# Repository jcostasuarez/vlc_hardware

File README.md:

# VLC Hardware — Comunicación por Luz Visible

Hardware abierto (KiCad) de una cadena de comunicación por luz visible (VLC):
transmisor óptico, receptor óptico de alta sensibilidad y placas de
acondicionamiento RF. Proyecto final de la carrera de Ingeniería Electrónica,
UTN FRBA.

Cada placa es un módulo independiente que se interconecta con cables coaxiales
SMA de 50 Ω. Todos los proyectos son **autocontenidos**: las huellas y los
símbolos están embebidos y copiados en la biblioteca local de cada proyecto, de
modo que se abren y verifican sin depender de bibliotecas externas.

## Arquitectura

```
Transmisor:   PRE ──► AMP ─┐
                         ├──► LED ──► (espacio libre, luz IR)
              PRE ──► FCA ─┘

Receptor:     PD ──► TIA ──► rx_amp ──► osciloscopio / ADC
```

- **TX**: `PRE` (red de preénfasis) excita a `AMP` **o** a `FCA`; el driver
  elegido alimenta la placa `LED`.
- **RX**: `PD` (fotodiodo + bias) entra a **una sola** placa `TIA`
  (`LMH34400` **o** `LTC6268-10`) y su salida pasa por `rx_amp`.
- **No instalar ambas TIA** en la misma cadena.

Detalle de cableado, alimentación y layout en
[docs/INTEGRACION_MODULAR.md](docs/INTEGRACION_MODULAR.md).

## Placas

| Proyecto | Ruta | Función |
|---|---|---|
| `rx_amp` | `Receiver/AMP/` | Amplificador receptor BGA616, SMA de entrada/salida y alimentación |
| `PD` | `Receiver/PD/` | Adaptador de fotodiodos PDB-C154SM / S5971 / SFH203, SMA y bias |
| `LMH34400` | `Receiver/TIA/LMH34400/` | TIA LMH34400 con entradas PD, salida RF y ALC |
| `LTC6268-10` | `Receiver/TIA/LTC6268-10/` | TIA LTC6268-10 con entrada PD y salida RF |
| `tx_amplifier` | `Transmitter/AMP/` | Amplificador de transmisión con SMA y alimentación de 3,3 V |
| `LumiCom_Transmitter` | `Transmitter/FCA/` | Amplificador/filtro de dos canales con OPA2675 (4 capas) |
| `LED` | `Transmitter/LED/` | Driver/emisor óptico IR, bobina y conectividad RF |
| `preenfasis` | `Transmitter/PRE/` | Red RF de preénfasis (variantes microstrip/CPW) |

## Estructura del repositorio

```
Receiver/AMP/            rx_amp.kicad_{pcb,sch} + library/
Receiver/PD/             PD.kicad_{pcb,sch} + Library/
Receiver/TIA/LMH34400/   LMH34400.kicad_{pcb,sch} + Library/
Receiver/TIA/LTC6268-10/ LTC6268-10.kicad_{pcb,sch} + Library/
Transmitter/AMP/         tx_amplifier.kicad_{pcb,sch} + footprints/
Transmitter/FCA/         LumiCom_Transmitter.kicad_{pcb,sch} + Library/
Transmitter/LED/         LED.kicad_{pcb,sch} + library/
Transmitter/PRE/         preenfasis.kicad_{pcb,sch} + library/
vna/                     Mediciones de red (VNA), calibraciones y scripts de análisis
docs/                    Integración, revisión y evidencias (ERC/DRC)
scripts/                 Exportación reproducible y herramientas de mantenimiento
```

Cada proyecto incluye su `fp-lib-table` y `sym-lib-table` que registran su
biblioteca local (`library/` o `Library/`).

## Requisitos

- [KiCad 10.0.6](https://www.kicad.org/) con `kicad-cli` en el `PATH`
  (variable `KICAD_CLI` para apuntar a otra ruta).
- Python 3 (sólo para las herramientas de `scripts/`).

## Generar revisión y fabricación

```bash
scripts/export_review.sh Receiver/TIA/LTC6268-10
```

Genera en `build/fabrication/<proyecto>/`:

- `erc.rpt`, `drc.rpt` y sus variantes de sólo errores;
- `schematic.pdf`, `layout.pdf`;
- `gerbers/` (Gerber + taladro Excellon);
- `positions.csv` (pick & place);
- `top.png`, `bottom.png` (render 3D) y `layers/board.svg`.

El script **falla** si ERC o DRC reportan errores. Con `STRICT=1` también falla
ante avisos.

## Simulaciones (ngspice)

Todas las simulaciones están unificadas en una única suite **ngspice**,
reproducible y sin GUI (`sim/`):

```bash
scripts/run_all_sims.sh                        # corre todo -> build/sim/
python3 scripts/run_spice.py sim/ltc6268-10/noise.cir --outdir build/sim --noise
python3 scripts/summarize_sims.py build/sim    # métricas -> docs/sim/RESULTS.md
```

`scripts/run_spice.py` usa la `libngspice` que viene con KiCad vía `ctypes`; no
requiere un binario `ngspice`. Incluye respuesta en frecuencia, transitorios y
**análisis de ruido** de las TIA (`lmh34400`, `ltc6268-10`). Los modelos TI
(LMH34400, OPA2675) y el BFR740 corren nativos, con los PSpice convertidos por
`scripts/convert_vendor_model.py`. Los supuestos y la fidelidad de cada deck
están en [sim/README.md](sim/README.md), y los resultados en
[docs/sim/RESULTS.md](docs/sim/RESULTS.md).

Además de cada placa, `sim/system/` interconecta la cadena completa
(`tx_chain`, `tx_chain_fca`, `rx_chain`, `link`, `link_channel`) con interfaces de
50 Ω, incluido el **canal óptico LED → fotodiodo con distancia paramétrica**. El
presupuesto de enlace y cómo ganar alcance están en
[docs/VLC_ALCANCE.md](docs/VLC_ALCANCE.md) (`scripts/vlc_link_budget.py`).

## Estado de revisión

Las ocho placas pasan **ERC y DRC con 0 errores y 0 avisos**, incluyendo DRC con
zonas rellenadas, paridad esquema-placa y paridad de bibliotecas de huellas y
símbolos. Los informes versionados están en
[docs/review/](docs/review/) y el informe completo en
[docs/REVISION_PCB.md](docs/REVISION_PCB.md).

Pendientes antes de fabricar:

1. Confirmar con el fabricante la pila real de 1,2 mm y sus dieléctricos para las
   trayectorias RF (placas `PRE`, `AMP`, TIA y `RX`).
2. Confirmar la decisión de no poblar `JP1` (`Test`) en `LMH34400`.

## Herramientas de mantenimiento

| Script | Uso |
|---|---|
| `scripts/summarize_netlists.py` | Resumen por placa de conectores, rieles y redes de alimentación |
| `scripts/vendor_footprints.py` | Copia las huellas embebidas a la biblioteca local y repunta los FPID |
| `scripts/vendor_symbols.py` | Copia los símbolos embebidos a la biblioteca local y repunta los `lib_id` |
| `scripts/sync_schematic_parity.py` | Sincroniza los campos de huella con el esquema (paridad) |

Todos aceptan modo *dry-run* (sin `--write`).

## Créditos

- Cotti, Nicolás Gabriel — `ncotti@frba.utn.edu.ar`
- UTN FRBA — Proyecto Final de Ingeniería Electrónica

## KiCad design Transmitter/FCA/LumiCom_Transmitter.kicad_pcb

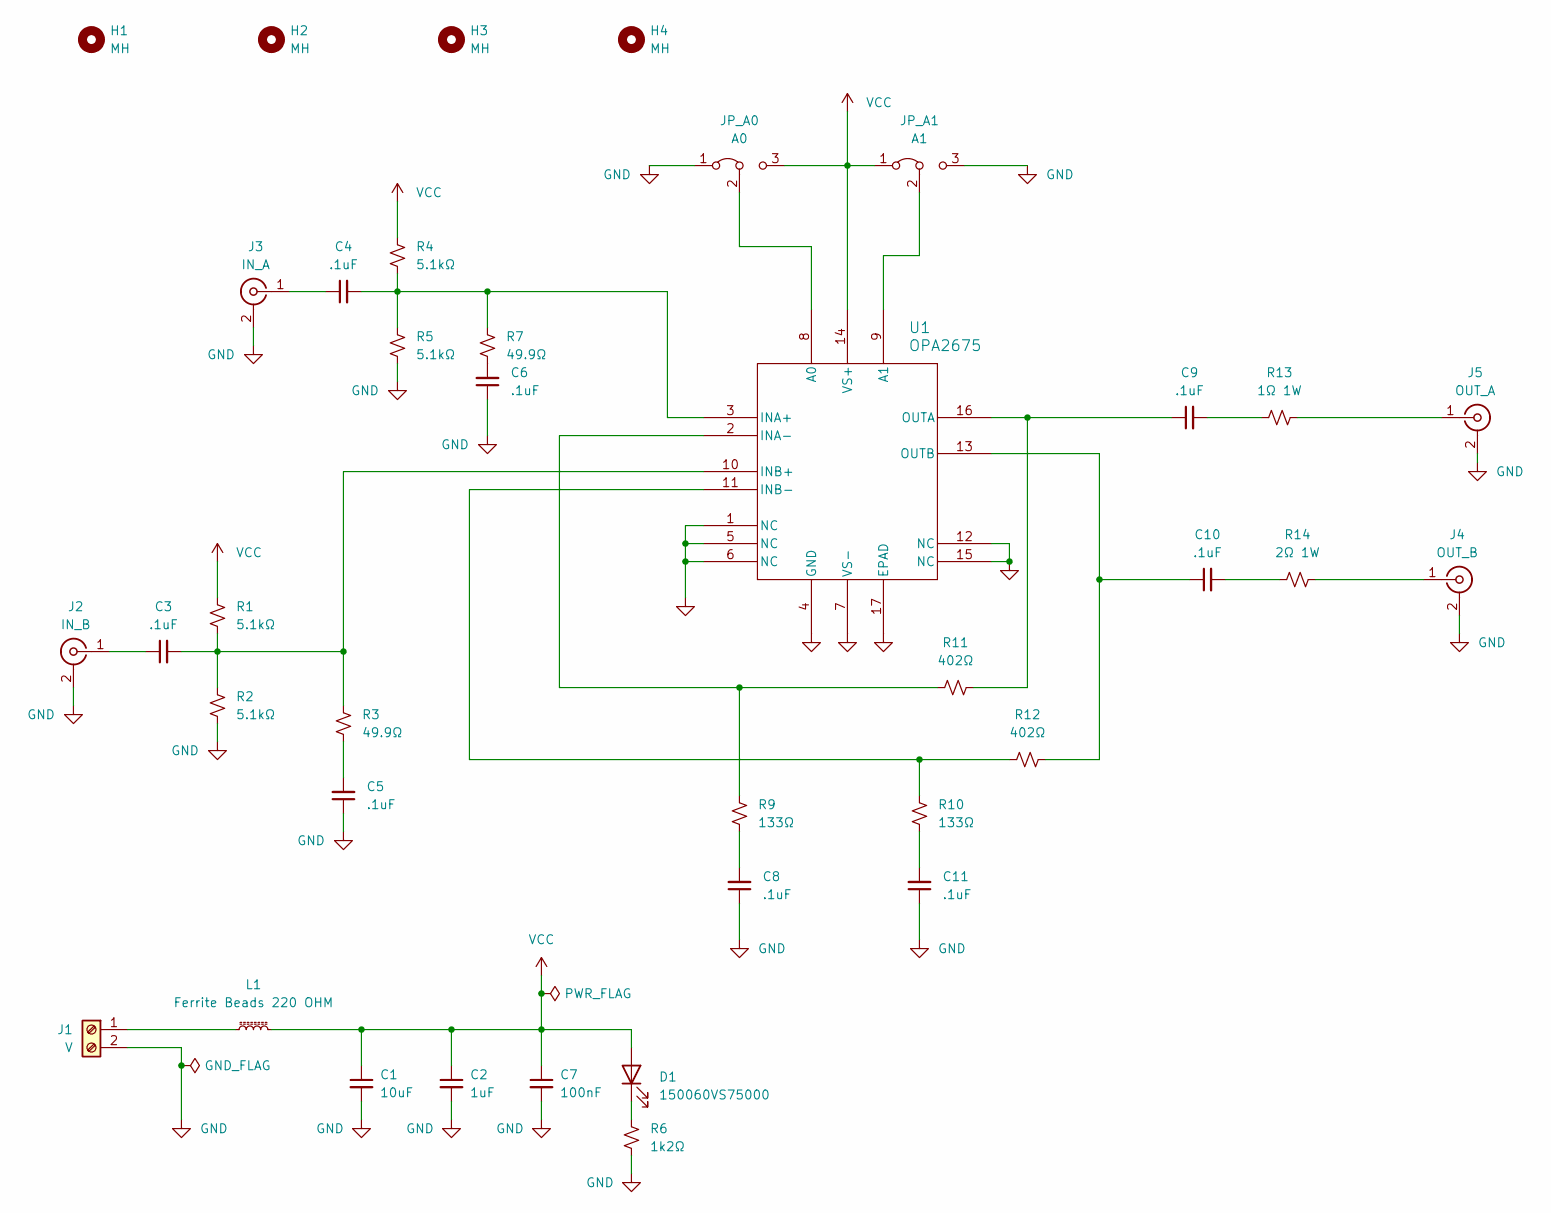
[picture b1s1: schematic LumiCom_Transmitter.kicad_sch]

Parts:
C1: 10uF; C_0603_1608Metric_Pad1.08x0.95mm_HandSolder; Manufacturer Part Number GRM188Z71A106MA73D; Mouser Part Number 81-GRM188Z71A106MA3D
C2: 1uF; C_0603_1608Metric_Pad1.08x0.95mm_HandSolder; Manufacturer Part Number CL10B105KP8NNNC; Mouser Part Number 187-CL10B105KP8NNNC
C3, C4, C5, C6, C8, C9, C10, C11: .1uF; C_0402_1005Metric_Pad0.74x0.62mm_HandSolder; Manufacturer Part Number 530L104KT16; Mouser Part Number 581-530L104KT16
C7: 100nF; C_0603_1608Metric_Pad1.08x0.95mm_HandSolder; Manufacturer Part Number CL10B104KO8NFNC; Mouser Part Number 187-CL10B104KO8NFNC
D1: 150060VS75000; LEDC1608X80N; Manufacturer Part Number 150060VS75000; Mouser Part Number 710-150060VS75000
H1, H2, H3, H4: MH; MountingHole_3.2mm_M3_ISO7380
J1: V; TerminalBlock_Phoenix_MKDS-1,5-2_1x02_P5.00mm_Horizontal
J2: IN_B; SMA_Samtec_SMA-J-P-X-ST-EM1_EdgeMount
J3: IN_A; SMA_Samtec_SMA-J-P-X-ST-EM1_EdgeMount
J4: OUT_B; SMA_Samtec_SMA-J-P-X-ST-EM1_EdgeMount
J5: OUT_A; SMA_Samtec_SMA-J-P-X-ST-EM1_EdgeMount
JP_A0: A0; PinHeader_1x03_P2.54mm_Vertical
JP_A1: A1; PinHeader_1x03_P2.54mm_Vertical
L1: Ferrite Beads 220 OHM; L_0603_1608Metric_Pad1.05x0.95mm_HandSolder; Manufacturer Part Number BLM18KG221SN1D; Mouser Part Number 81-BLM18KG221SN1D
R1, R2, R4, R5: 5.1kΩ; R_0603_1608Metric; Manufacturer Part Number CRCW06035K10FKEA; Mouser Part Number 71-CRCW0603-5.1K-E3
R3, R7: 49.9Ω; R_0603_1608Metric; Manufacturer Part Number MCT06030C4999FP500; Mouser Part Number 594-MCT06030C4999FP5
R6: 1k2Ω; R_0603_1608Metric_Pad0.98x0.95mm_HandSolder; Manufacturer Part Number CRCW06031K20FKEA; Mouser Part Number 71-CRCW0603-1.2K-E3
R9, R10: 133Ω; R_0402_1005Metric_Pad0.72x0.64mm_HandSolder; Manufacturer Part Number CRT0402-FZ-1330GLF; Mouser Part Number 652-CRT0402FZ1330GLF
R11, R12: 402Ω; R_0402_1005Metric_Pad0.72x0.64mm_HandSolder; Manufacturer Part Number CRT0402-FZ-4020GLF; Mouser Part Number 652-CRT0402FZ4020GLF
R13: 1Ω 1W; R_1206_3216Metric_Pad1.30x1.75mm_HandSolder; Manufacturer Part Number RNCL1206FT1R00; Mouser Part Number 708-RNCL1206FT1R00
R14: 2Ω 1W; R_1206_3216Metric_Pad1.30x1.75mm_HandSolder; Manufacturer Part Number RNCL1206FT2R00; Mouser Part Number 708-RNCL1206FT2R00
U1: OPA2675; Texas_OPA2675; Manufacturer Part Number OPA2675RGVR; Mouser Part Number 595-OPA2675RGVR

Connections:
GND: C1.2, C2.2, C5.1, C6.1, C7.2, C8.1, C11.1, J1.2, J2.2 (Ext), J3.2 (Ext), J4.2 (Ext), J5.2 (Ext), JP_A0.1 (A), JP_A1.3 (B), R2.2, R5.2, R6.2, U1.1 (NC), U1.4 (GND), U1.5 (NC), U1.6 (NC), U1.7 (VS-), U1.12 (NC), U1.15 (NC), U1.17 (EPAD)
unnamed: C5.2, R3.2
unnamed: C6.2, R7.2
unnamed: C8.2, R9.1
unnamed: C9.2, R13.1
unnamed: C10.2, R14.1
unnamed: C11.2, R10.1
unnamed: D1.1 (K), R6.1
unnamed: J1.1, L1.1
unnamed: C3.1, J2.1 (In)
unnamed: C4.1, J3.1 (In)
unnamed: J4.1 (In), R14.2
unnamed: J5.1 (In), R13.2
unnamed: JP_A0.2 (C), U1.8 (A0)
unnamed: JP_A1.2 (C), U1.9 (A1)
unnamed: C4.2, R4.2, R5.1, R7.1, U1.3 (INA+)
unnamed: R9.2, R11.1, U1.2 (INA-)
unnamed: C3.2, R1.2, R2.1, R3.1, U1.10 (INB+)
unnamed: R10.2, R12.1, U1.11 (INB-)
unnamed: C9.1, R11.2, U1.16 (OUTA)
unnamed: C10.1, R12.2, U1.13 (OUTB)
VCC: C1.1, C2.1, C7.1, D1.2 (A), JP_A0.3 (B), JP_A1.1 (A), L1.2, R1.1, R4.1, U1.14 (VS+)

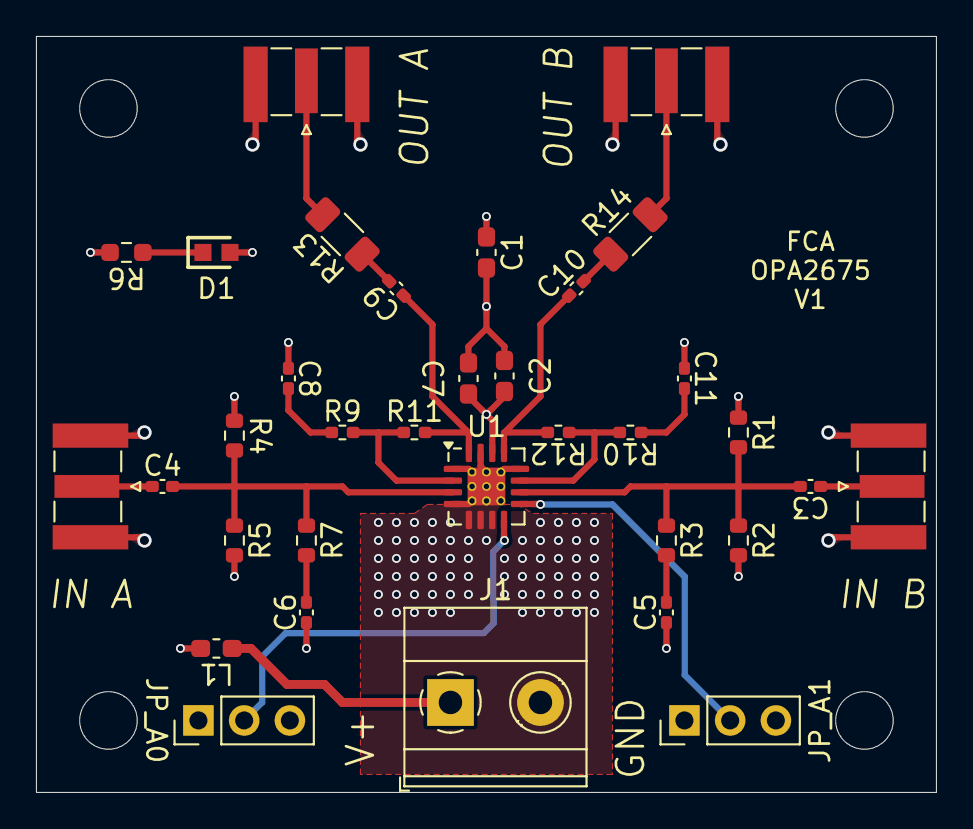
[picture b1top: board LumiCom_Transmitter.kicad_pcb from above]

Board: 4 copper layers, 50.0 x 42.0 mm, 38 parts (0 on the bottom side), 22 nets.

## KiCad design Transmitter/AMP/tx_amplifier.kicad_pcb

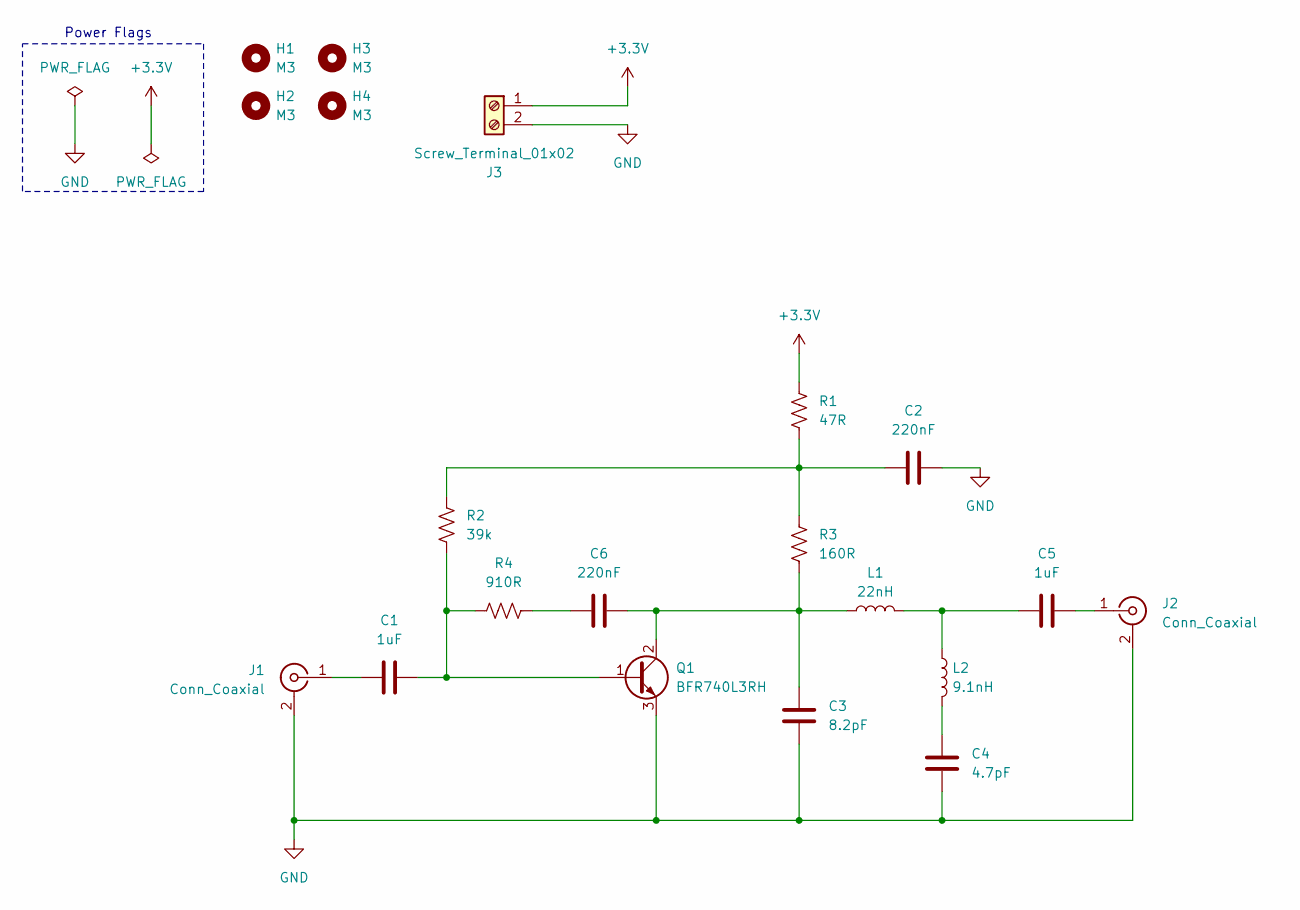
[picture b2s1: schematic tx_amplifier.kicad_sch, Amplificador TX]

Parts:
C1, C5: 1uF; C_0603_1608Metric_Pad1.08x0.95mm_HandSolder; Manufacturer P/N SH18B105K160CT; Mouser P/N 791-SH18B105K160CT
C2, C6: 220nF; C_0603_1608Metric_Pad1.08x0.95mm_HandSolder; Manufacturer P/N 0603B224K250CT; Mouser P/N 791-0603B224K250CT
C3: 8.2pF; C_0603_1608Metric_Pad1.08x0.95mm_HandSolder; Manufacturer P/N 0603N8R2C500CT; Mouser P/N 791-0603N8R2C500CT
C4: 4.7pF; C_0603_1608Metric_Pad1.08x0.95mm_HandSolder; Manufacturer P/N 0603N4R7C500CT; Mouser P/N 791-0603N4R7C500CT
H1, H2, H3, H4: M3; MountingHole_3.2mm_M3_ISO7380; Manufacturer P/N N/A; Mouser P/N N/A
J1, J2: Conn_Coaxial; SMA_Samtec_SMA-J-P-X-ST-EM1_EdgeMount; Manufacturer P/N SMA-KE1.2mm; Mouser P/N N/A
J3: Screw_Terminal_01x02; TerminalBlock_bornier-2_P5.08mm; Manufacturer P/N VI0221550000G; Mouser P/N 649-220316-H021B01LF
L1: 22nH; L_0603_1608Metric_Pad1.05x0.95mm_HandSolder; Manufacturer P/N 7847806220; Mouser P/N 710-7847806220
L2: 9.1nH; L_0603_1608Metric_Pad1.05x0.95mm_HandSolder; Manufacturer P/N LQW18AN9N1C00D; Mouser P/N 81-LQW18AN9N1C00D
Q1: BFR740L3RH; TSLP-3-9; Manufacturer P/N BFR740L3RHE6327XTSA1; Mouser P/N 726-BFR740L3RHE6327X
R1: 47R; R_1206_3216Metric_Pad1.30x1.75mm_HandSolder; Manufacturer P/N RC1206FR-0747RL; Mouser P/N 603-RC1206FR-0747RL
R2: 39k; R_0603_1608Metric_Pad0.98x0.95mm_HandSolder; Manufacturer P/N RT0603FRE0739KL; Mouser P/N 603-RT0603FRE0739KL
R3: 160R; R_1206_3216Metric_Pad1.30x1.75mm_HandSolder; Manufacturer P/N RC1206FR-07160RL; Mouser P/N 603-RC1206FR-07160RL
R4: 910R; R_0603_1608Metric_Pad0.98x0.95mm_HandSolder; Manufacturer P/N RT0603FRE07910RL; Mouser P/N 603-RT0603FRE07910RL

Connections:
+3.3V: J3.1, R1.2
GND: C2.2, C3.1, C4.1, J1.2 (Ext), J2.2 (Ext), J3.2, Q1.3 (E)
unnamed: C2.1, R1.1, R2.2, R3.2
unnamed: C4.2, L2.2
unnamed: C5.1, L1.2, L2.1
unnamed: C6.1, R4.1
unnamed: C1.1, J1.1 (In)
unnamed: C5.2, J2.1 (In)
unnamed: C1.2, Q1.1 (B), R2.1, R4.2
unnamed: C3.2, C6.2, L1.1, Q1.2 (C), R3.1

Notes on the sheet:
Power Flags

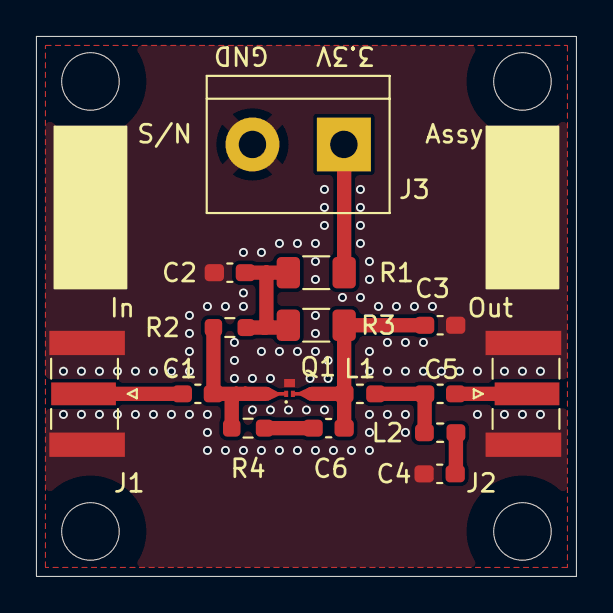
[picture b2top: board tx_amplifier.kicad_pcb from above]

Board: 2 copper layers, 30.0 x 30.0 mm, 20 parts (0 on the bottom side), 10 nets.

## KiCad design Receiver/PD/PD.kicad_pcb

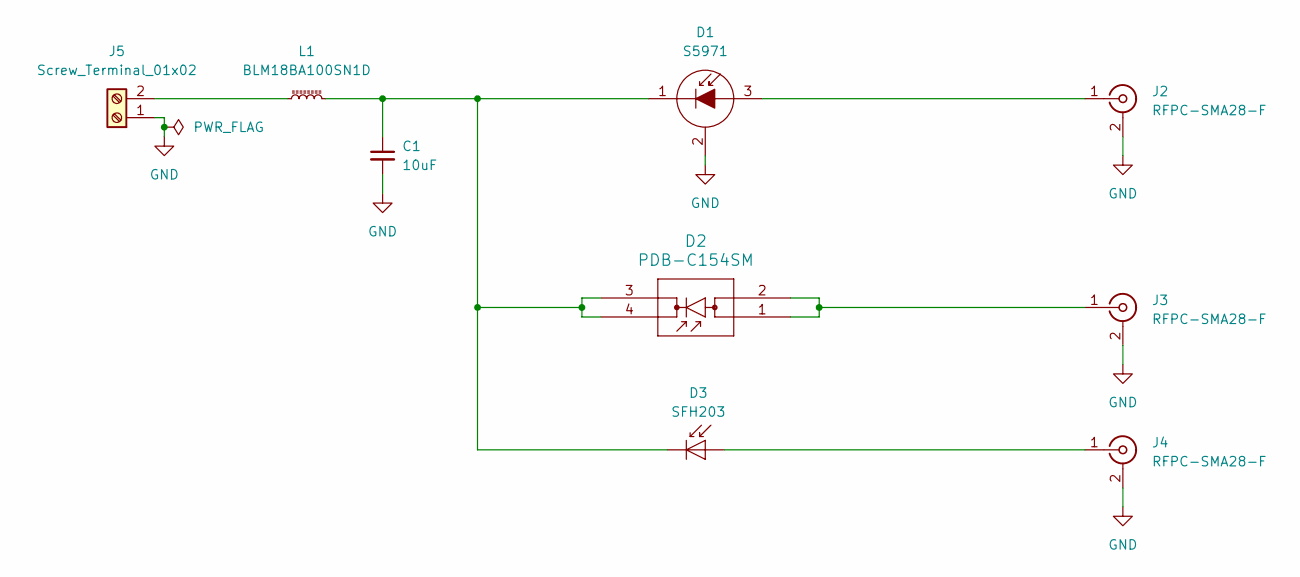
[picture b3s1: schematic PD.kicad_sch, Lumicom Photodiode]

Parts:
C1: 10uF; C_0603_1608Metric_Pad1.08x0.95mm_HandSolder
D1: S5971; TO-18-3; Mfr P/N S5971
D2: PDB-C154SM; PDB-C154SM_ADP; Mfr P/N PDB-C154SM; Mouser P/N 846-PDB-C154SM
D3: SFH203; LED_D5.0mm_IRGrey; Mfr P/N SFH 203 P; Mouser P/N 720-SFH203P
J2, J3, J4: RFPC-SMA28-F
J5: Screw_Terminal_01x02; TerminalBlock_bornier-2_P5.08mm
L1: BLM18BA100SN1D; L_0603_1608Metric_Pad1.05x0.95mm_HandSolder

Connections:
GND: C1.2, D1.2 (C), J2.2 (Ext), J3.2 (Ext), J4.2 (Ext), J5.1
unnamed: D1.3 (A), J2.1 (In)
unnamed: C1.1, D1.1 (K), D2.3 (CATHODE), D2.4 (CATHODE), D3.1 (K), L1.2
unnamed: D3.2 (A), J4.1 (In)
unnamed: D2.1 (ANODE), D2.2 (ANODE), J3.1 (In)
unnamed: J5.2, L1.1

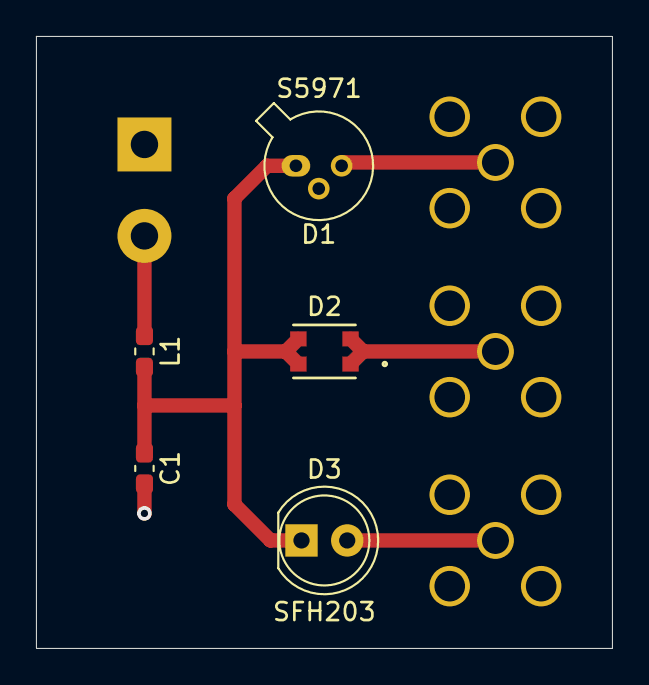
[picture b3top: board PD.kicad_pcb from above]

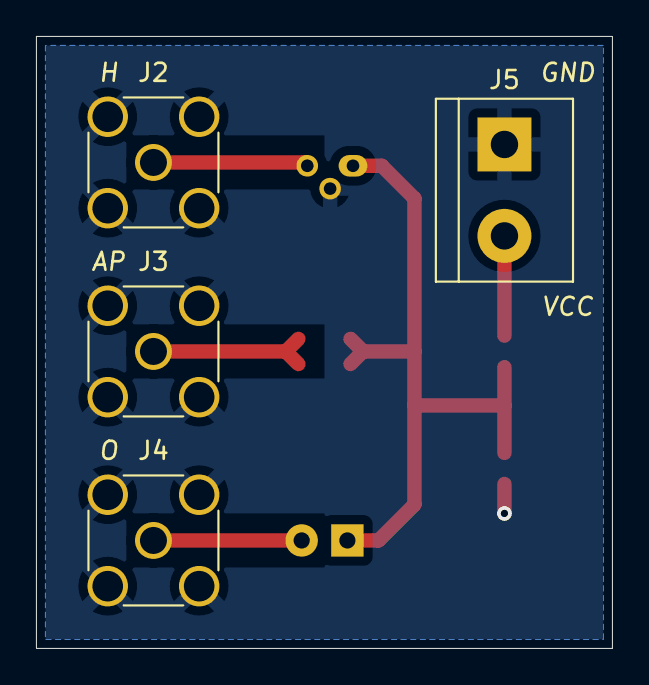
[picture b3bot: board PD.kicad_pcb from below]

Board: 2 copper layers, 32.0 x 34.0 mm, 9 parts (4 on the bottom side), 6 nets.

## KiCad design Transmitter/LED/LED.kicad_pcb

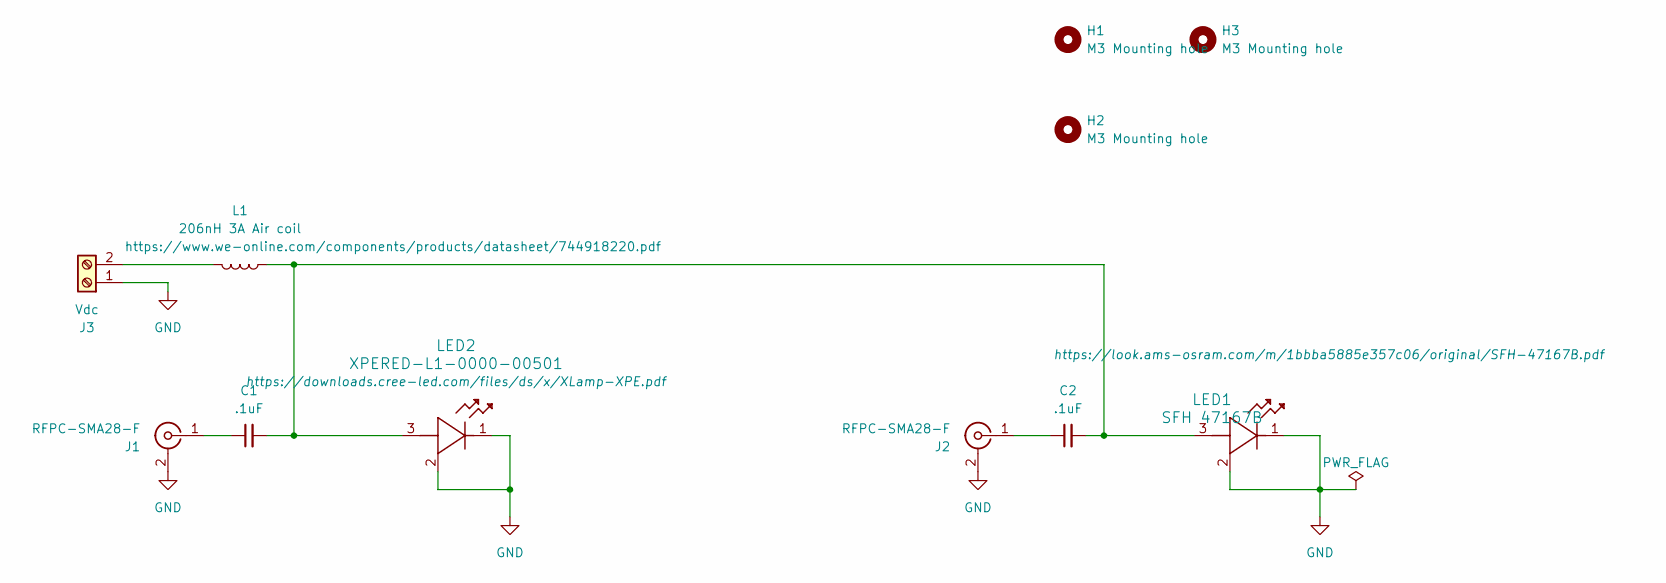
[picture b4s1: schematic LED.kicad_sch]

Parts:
C1, C2: .1uF; C_0402_1005Metric_Pad0.74x0.62mm_HandSolder; Manufacturer Part Number 530L104KT16; Mouser Part Number 581-530L104KT16
H1, H2, H3: M3 Mounting hole; MountingHole_3.2mm_M3_DIN965
J1, J2: RFPC-SMA28-F; Manufacturer Part Number RFPC-SMA28-F; Mouser Part Number 640-RFPCSMA28F
J3: Vdc; TerminalBlock_Phoenix_MKDS-1,5-2_1x02_P5.00mm_Horizontal
L1: 206nH 3A Air coil; L_Wurth_WE-CAIR-5910; Manufacturer Part Number 744918220; Mouser Part Number 710-744918220
LED1: SFH 47167B
LED2: XPERED-L1-0000-00501; LED_CREE_XPLx

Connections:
GND: J1.2 (Ext), J2.2 (Ext), J3.1, LED1.1 (cathode), LED1.2 (thermal), LED2.1 (cathode), LED2.2 (thermal)
unnamed: C1.1, J1.1 (In)
unnamed: C2.1, J2.1 (In)
unnamed: J3.2, L1.2
unnamed: C1.2, C2.2, L1.1, LED1.3 (anode), LED2.3 (anode)

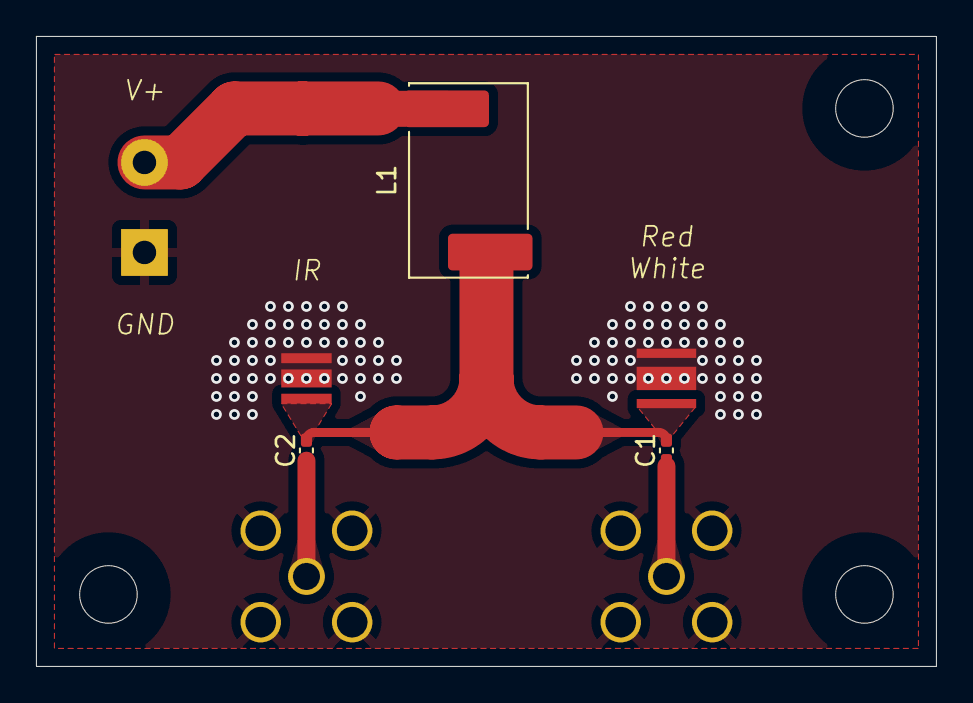
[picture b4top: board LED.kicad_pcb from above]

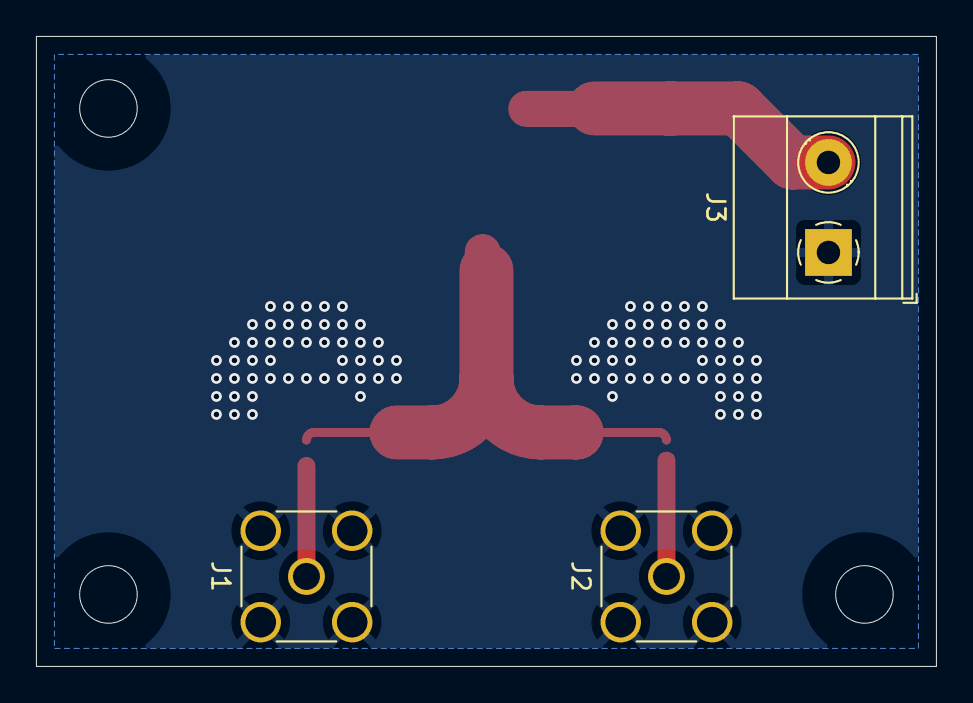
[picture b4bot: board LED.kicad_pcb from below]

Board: 2 copper layers, 50.0 x 35.0 mm, 11 parts (3 on the bottom side), 5 nets.

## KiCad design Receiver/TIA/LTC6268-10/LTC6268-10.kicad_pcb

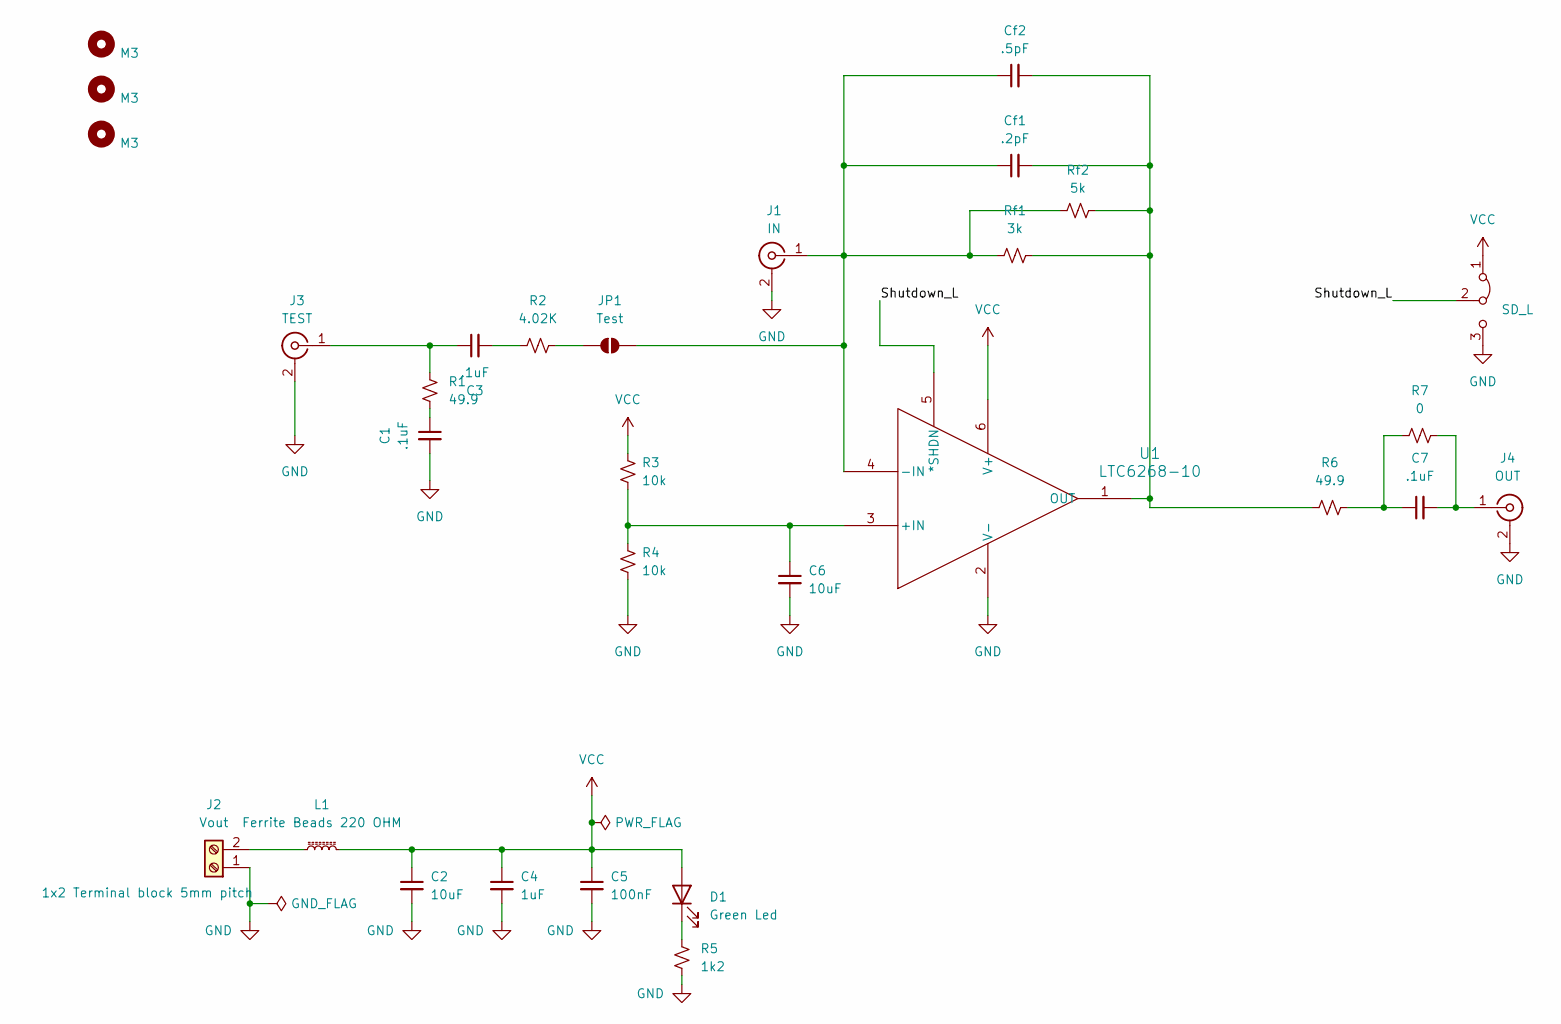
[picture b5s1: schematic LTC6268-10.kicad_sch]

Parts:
C1, C3, C7: .1uF; C_0402_1005Metric_Pad0.74x0.62mm_HandSolder; Manufacturer Part Number 530L104KT16; Mouser Part Number 581-530L104KT16
C2, C6: 10uF; C_0603_1608Metric_Pad1.08x0.95mm_HandSolder; Manufacturer Part Number GRM188Z71A106MA73D; Mouser Part Number 81-GRM188Z71A106MA3D
C4: 1uF; C_0603_1608Metric_Pad1.08x0.95mm_HandSolder; Manufacturer Part Number CL10B105KP8NNNC; Mouser Part Number 187-CL10B105KP8NNNC
C5: 100nF; C_0603_1608Metric_Pad1.08x0.95mm_HandSolder; Manufacturer Part Number CL10B104KO8NFNC; Mouser Part Number 187-CL10B104KO8NFNC
Cf1: .2pF; C_0402_1005Metric; Manufacturer Part Number 04023J0R2ZBSTR; Mouser Part Number 581-04023J0R2ZBSTR
Cf2: .5pF; C_0402_1005Metric; Manufacturer Part Number 04023J0R5BBSTR; Mouser Part Number 581-04023J0R5BBSTR
D1: Green Led; LED_0603_1608Metric; Manufacturer Part Number 150060VS75000; Mouser Part Number 710-150060VS75000
H1, H2, H3: M3; MountingHole_3.2mm_M3_DIN965
J1: IN; SMA_Samtec_SMA-J-P-X-ST-EM1_EdgeMount
J2: Vout; TerminalBlock_Phoenix_MKDS-1,5-2_1x02_P5.00mm_Horizontal
J3: TEST; SMA_Samtec_SMA-J-P-X-ST-EM1_EdgeMount
J4: OUT; SMA_Samtec_SMA-J-P-X-ST-EM1_EdgeMount
JP1: Test; R_0603_1608Metric_Pad0.98x0.95mm_HandSolder; Manufacturer Part Number MCT0603MZ0000ZP500; Mouser Part Number 594-MCT0603MZ0000ZP5
L1: Ferrite Beads 220 OHM; L_0603_1608Metric_Pad1.05x0.95mm_HandSolder; Manufacturer Part Number BLM18KG221SN1D; Mouser Part Number 81-BLM18KG221SN1D
R1, R6: 49.9; R_0603_1608Metric_Pad0.98x0.95mm_HandSolder; Manufacturer Part Number MCT06030C4999FP500; Mouser Part Number 594-MCT06030C4999FP5
R2: 4.02K; R_0603_1608Metric_Pad0.98x0.95mm_HandSolder; Manufacturer Part Number MCT06030C4021FP500; Mouser Part Number 594-MCT06030C4021FP5
R3, R4: 10k; R_0603_1608Metric_Pad0.98x0.95mm_HandSolder; Manufacturer Part Number CRCW060310K0FKEI; Mouser Part Number 71-CRCW060310K0FKEI
R5: 1k2; R_0603_1608Metric_Pad0.98x0.95mm_HandSolder; Manufacturer Part Number CRCW06031K20FKEA; Mouser Part Number 71-CRCW0603-1.2K-E3
R7: 0; R_0603_1608Metric_Pad0.98x0.95mm_HandSolder; Manufacturer Part Number MCT0603MZ0000ZP500; Mouser Part Number 594-MCT0603MZ0000ZP5
Rf1: 3k; R_0402_1005Metric; Manufacturer Part Number MCS04020D3001BE000; Mouser Part Number 594-MCS04020D3001BE0
Rf2: 5k; R_0402_1005Metric; Manufacturer Part Number MCS04020C4991FE000; Mouser Part Number 594-MCS04020C4991FE0
SD_L1: SD_L; PinHeader_1x03_P2.54mm_Vertical
U1: LTC6268-10; TSOT-23_S6_LIT; Manufacturer Part Number LTC6268IS6-10#TRMPBF; Mouser Part Number 584-C6268IS6-10TMPF

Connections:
/Shutdown_L: SD_L1.2 (C), U1.5 (*SHDN)
GND: C1.2, C2.2, C4.2, C5.2, C6.2, J1.2 (Ext), J2.1, J3.2 (Ext), J4.2 (Ext), R4.2, R5.2, SD_L1.3 (B), U1.2 (V-)
unnamed: C1.1, R1.2
unnamed: C3.2, R2.1
unnamed: C7.1, R6.2, R7.1
unnamed: D1.1 (K), R5.1
unnamed: Cf1.1, Cf2.1, J1.1 (In), JP1.2 (B), Rf1.1, Rf2.1, U1.4 (-IN)
unnamed: J2.2, L1.1
unnamed: C3.1, J3.1 (In), R1.1
unnamed: C7.2, J4.1 (In), R7.2
unnamed: JP1.1 (A), R2.2
unnamed: C6.1, R3.2, R4.1, U1.3 (+IN)
unnamed: Cf1.2, Cf2.2, R6.1, Rf1.2, Rf2.2, U1.1 (OUT)
VCC: C2.1, C4.1, C5.1, D1.2 (A), L1.2, R3.1, SD_L1.1 (A), U1.6 (V+)

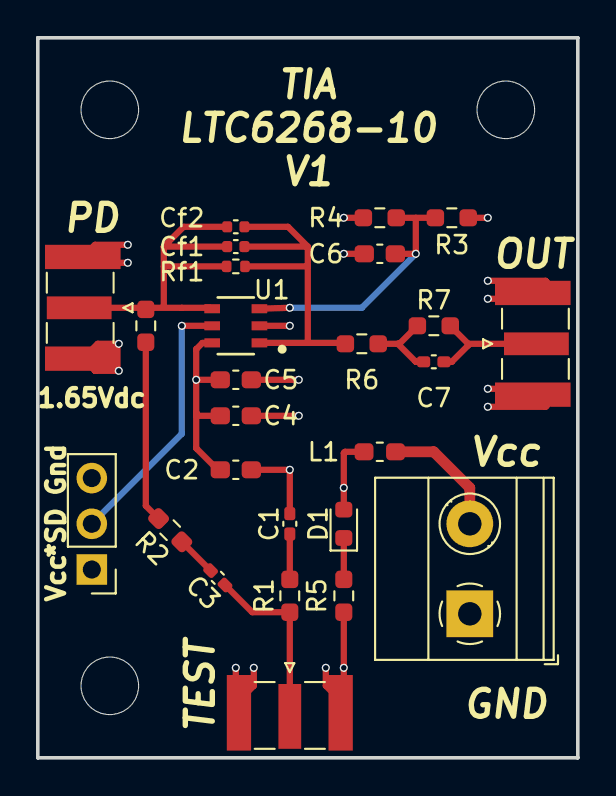
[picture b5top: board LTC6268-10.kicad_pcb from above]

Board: 4 copper layers, 30.0 x 40.0 mm, 29 parts (0 on the bottom side), 14 nets.

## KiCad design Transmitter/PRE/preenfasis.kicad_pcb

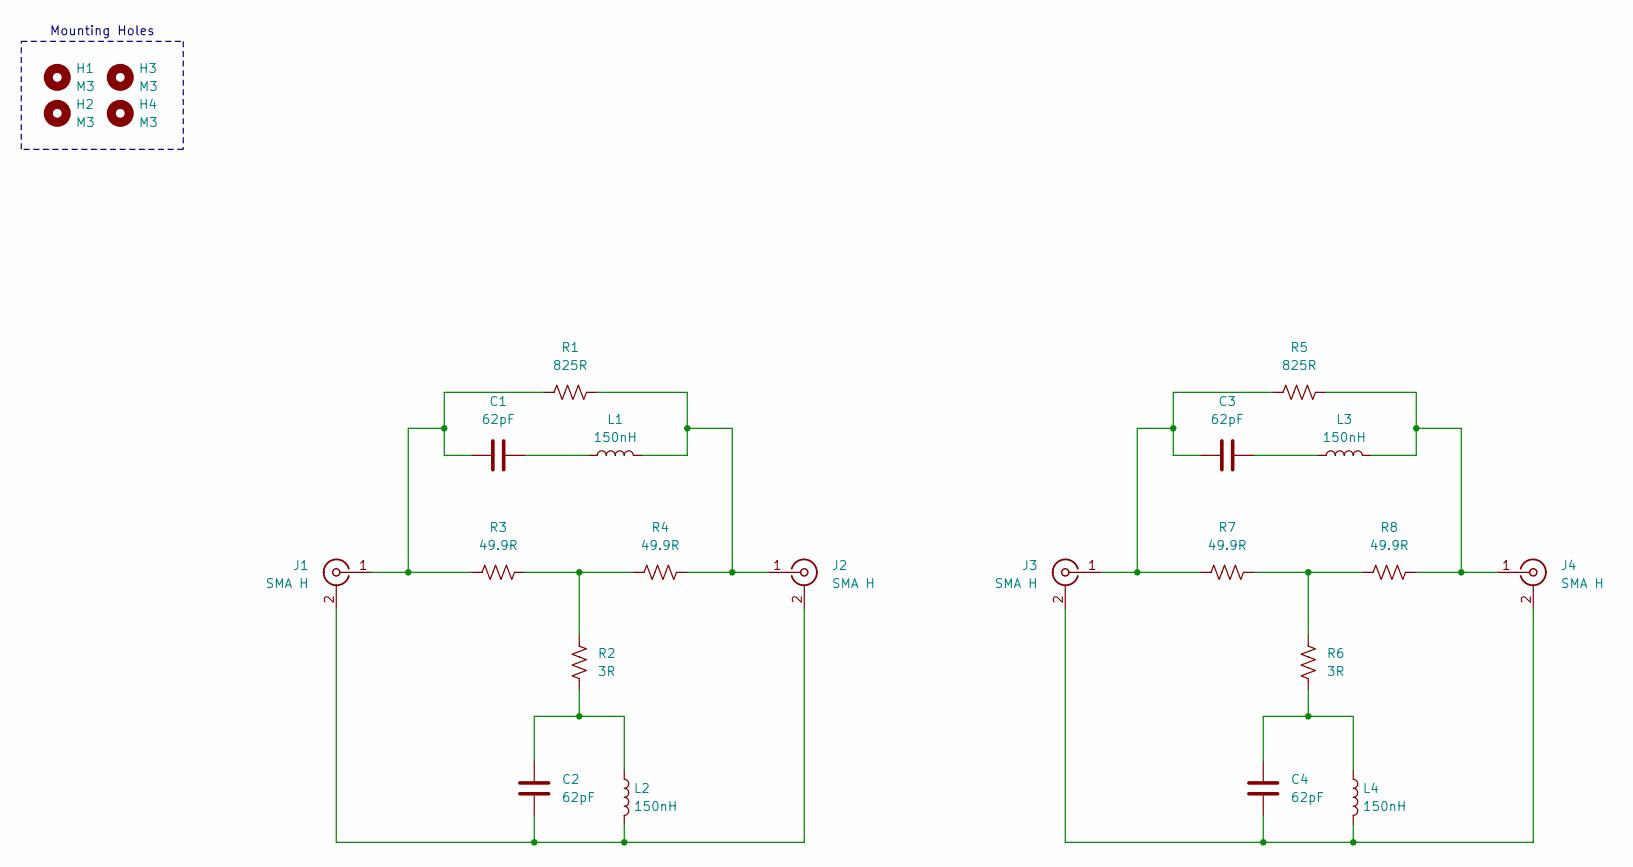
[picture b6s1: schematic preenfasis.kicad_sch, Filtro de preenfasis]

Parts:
C1, C2, C3, C4: 62pF; C_0603_1608Metric_Pad1.08x0.95mm_HandSolder; Manufacturer P/N CC0603JRNPO9BN620; Mouser P/N 603-CC603JRNPO9BN620
H1, H2, H3, H4: M3; MountingHole_3.2mm_M3_ISO7380; Manufacturer P/N N/A; Mouser P/N N/A
J1, J2, J3, J4: SMA H; SMA_Samtec_SMA-J-P-X-ST-EM1_EdgeMount; Manufacturer P/N Electrocomponentes; Mouser P/N N/A
L1, L2, L3, L4: 150nH; L_0603_1608Metric_Pad1.05x0.95mm_HandSolder; Manufacturer P/N MLJ1608WR15JT000; Mouser P/N 810-MLJ1608WR15JT000
R1, R5: 825R; R_0603_1608Metric_Pad0.98x0.95mm_HandSolder; Manufacturer P/N RT0603FRE07825RL; Mouser P/N 603-RT0603FRE07825RL
R2, R6: 3R; R_0603_1608Metric_Pad0.98x0.95mm_HandSolder; Manufacturer P/N RT0603FRE073RL; Mouser P/N 603-RT0603FRE073RL
R3, R4, R7, R8: 49.9R; R_0603_1608Metric_Pad0.98x0.95mm_HandSolder; Manufacturer P/N RT0603FRE0749R9L; Mouser P/N 603-RT0603FRE0749R9L

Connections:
unnamed: C1.2, L1.1
unnamed: C2.2, L2.1, R2.2
unnamed: C3.2, L3.1
unnamed: C4.2, L4.1, R6.2
unnamed: C2.1, J1.2 (Ext), J2.2 (Ext), L2.2
unnamed: C1.1, J1.1 (In), R1.1, R3.1
unnamed: J2.1 (In), L1.2, R1.2, R4.2
unnamed: C4.1, J3.2 (Ext), J4.2 (Ext), L4.2
unnamed: C3.1, J3.1 (In), R5.1, R7.1
unnamed: J4.1 (In), L3.2, R5.2, R8.2
unnamed: R2.1, R3.2, R4.1
unnamed: R6.1, R7.2, R8.1

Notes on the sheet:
Mounting Holes

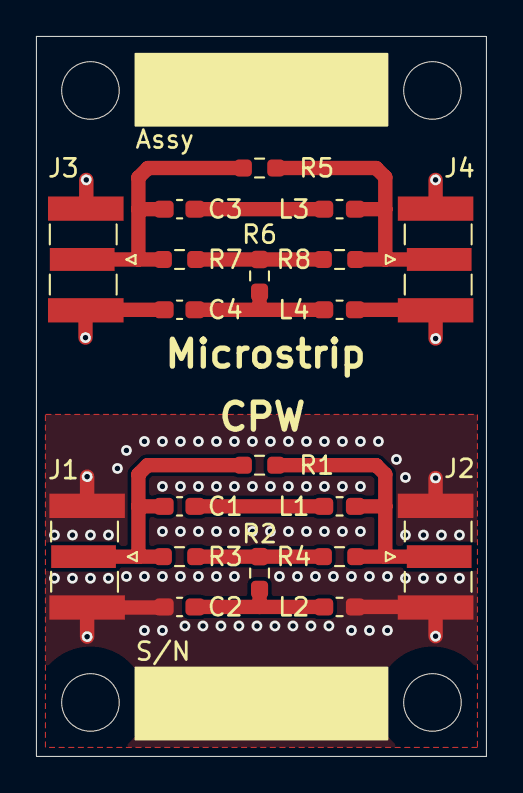
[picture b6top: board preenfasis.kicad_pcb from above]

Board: 2 copper layers, 25.0 x 40.0 mm, 24 parts (0 on the bottom side), 12 nets.
